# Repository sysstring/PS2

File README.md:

# PS2
LM317 based CC/CV power supply

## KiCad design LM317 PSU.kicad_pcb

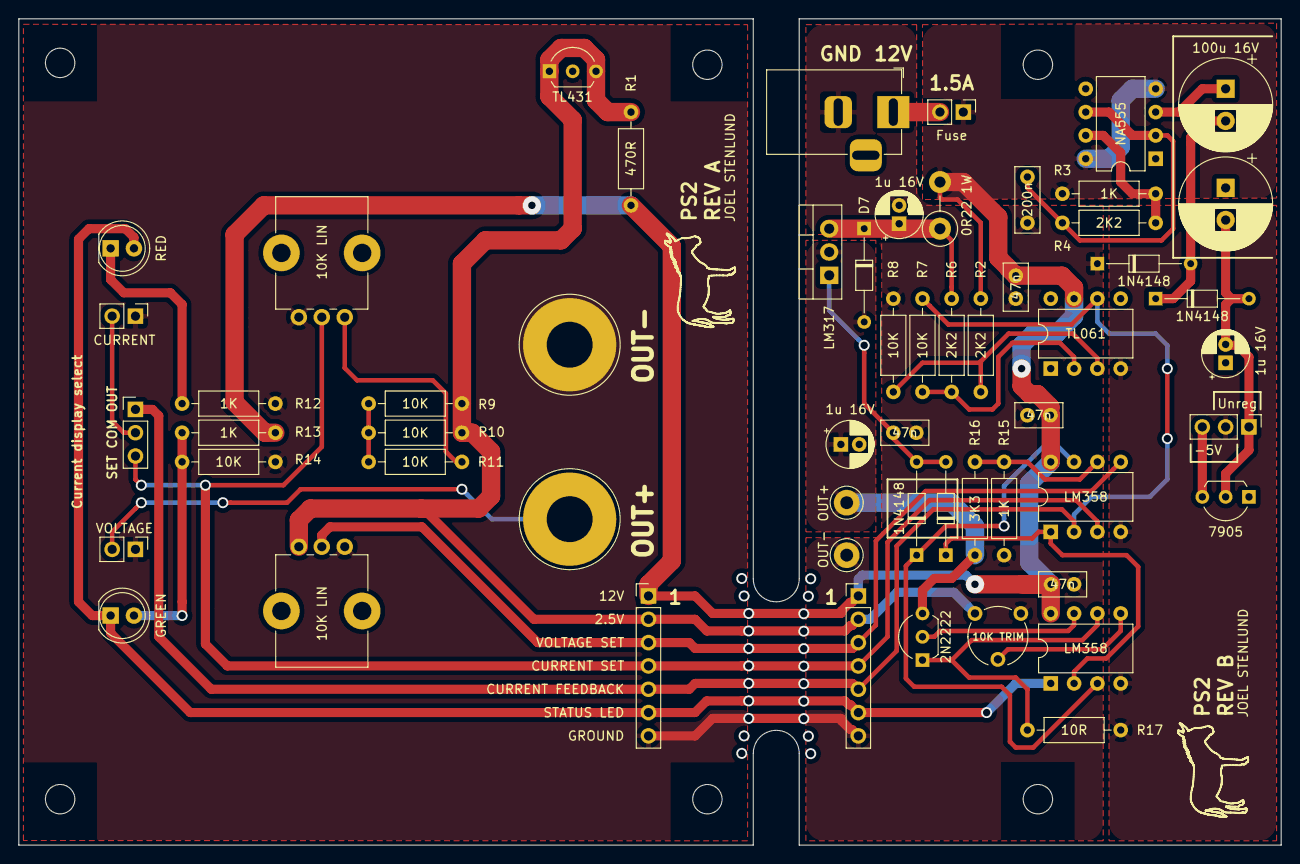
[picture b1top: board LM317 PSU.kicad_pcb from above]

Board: 2 copper layers, 137.5 x 90.0 mm, 63 parts (0 on the bottom side), 31 nets.

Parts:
C1: 200n; C_Rect_L7.0mm_W2.5mm_P5.00mm
C2: 100u 16V; CP_Radial_D10.0mm_P3.50mm
C3: 100u 16v; CP_Radial_D10.0mm_P3.50mm
C4, C6, C8, C9: 47n; C_Disc_D5.0mm_W2.5mm_P2.50mm
C5, C7, C10: 1u 16V; CP_Radial_D5.0mm_P2.00mm
D1: TL431; TO-92L_Inline_Wide
D2, D3, D6, D8: 1N4148; D_DO-34_SOD68_P10.16mm_Horizontal
D4: GREEN; LED_D5.0mm
D5: RED; LED_D5.0mm
D7: 1N4007; D_DO-34_SOD68_P10.16mm_Horizontal
F1: Fuse; PinHeader_1x02_P2.54mm_Vertical
J1: OUT+; Banana_Jack_1Pin
J2: OUT-; Banana_Jack_1Pin
J3: Barrel_Jack_MountingPin; BarrelJack_Horizontal
J4: Conn_01x07_Male; PinHeader_1x07_P2.54mm_Vertical
J5: Conn_01x07_Female; PinHeader_1x07_P2.54mm_Vertical
J7: Conn_01x01_Female; TestPoint_Loop_D3.50mm_Drill1.4mm_Beaded
J8: V- jumper; PinHeader_1x03_P2.54mm_Vertical
MES1: CURRENT; PinHeader_1x02_P2.54mm_Vertical
MES2: VOLTAGE; PinHeader_1x02_P2.54mm_Vertical
MH1, MH2, MH3, MH4, MH5, MH8: MountingHole; MountingHole_3.2mm_M3
OUT+: Conn_01x01_Female; TestPoint_Loop_D3.50mm_Drill1.4mm_Beaded
Q1: 2N2222; TO-92L_Inline_Wide
R1: 470R; R_Axial_DIN0207_L6.3mm_D2.5mm_P10.16mm_Horizontal
R2, R4, R6: 2K2; R_Axial_DIN0207_L6.3mm_D2.5mm_P10.16mm_Horizontal
R3, R12, R13, R16: 1K; R_Axial_DIN0207_L6.3mm_D2.5mm_P10.16mm_Horizontal
R5: 0R22 1W; R_Axial_DIN0411_L9.9mm_D3.6mm_P5.08mm_Vertical
R7, R8, R9, R10, R11, R14: 10K; R_Axial_DIN0207_L6.3mm_D2.5mm_P10.16mm_Horizontal
R15: 3K3; R_Axial_DIN0207_L6.3mm_D2.5mm_P10.16mm_Horizontal
R17: 10R; R_Axial_DIN0207_L6.3mm_D2.5mm_P10.16mm_Horizontal
RV1, RV2: 10K LIN; Potentiometer_Alps_RK09K_Single_Vertical
RV3: 10K TRIM; Potentiometer_Piher_PT-6-V_Vertical
SW1: Current display select; PinHeader_1x03_P2.54mm_Vertical
U1: NA555; DIP-8_W7.62mm
U2: TL061; DIP-8_W7.62mm
U3, U5: LM358; DIP-8_W7.62mm
U4: LM317; TO-220-3_Vertical
U6: 7905; TO-92L_Inline_Wide

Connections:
2V5: D1.1, D1.3, J4.2, J5.2, R1.1, R9.2, R10.2, RV2.1, RV3.1
12V_F: C4.2, C8.2, C9.2, F1.1, J4.1, J5.1, R1.2, R2.1, R3.1, R5.2, R13.1, U1.4, U1.8, U2.7, U3.8, U5.8
+12V: F1.2, J3.1
/Hi_side_sense: R2.2, R7.2, U2.3
/I_cmp: D6.1, U3.2, U5.1
/I_sink_sense: Q1.1, R17.2, U3.6
/Lo_side_sense: R6.2, R8.1, U2.2
/REG_INP: C5.1, D7.1, R5.1, R6.1, U4.3
/V_ADJ: C6.1, D6.2, D8.2, U4.1
/V_cmp: D8.1, U3.3, U5.7
GNDA: C1.1, C3.1, C4.1, C5.2, C6.2, C7.2, C8.1, C9.1, C10.1, D1.2, D3.1, J2.1, J3.2, J4.7, J5.7, J7.1, MES1.1, MES2.1, R7.1, R12.1, R14.1, R16.1, RV1.3, RV2.3, RV3.3, U1.1, U6.1
I_FB: J4.5, J5.5, R8.2, SW1.1, U2.6, U5.2
I_SET: J4.4, J5.4, RV1.2, SW1.3, U5.3
LED: D4.1, D5.2, J4.6, J5.6, U3.1
unnamed: C1.2, R4.2, U1.2, U1.6
unnamed: C2.1, U1.3
unnamed: C2.2, D2.1, D3.2
unnamed: C3.2, C10.2, D2.2, J8.1, U6.2
unnamed: D4.2, R13.2, R14.2
unnamed: D5.1, R12.2
unnamed: J8.3, U6.3
unnamed: MES1.2, SW1.2
unnamed: Q1.2, U3.7
unnamed: R3.2, R4.1, U1.7
unnamed: R9.1, R10.1, R11.1
unnamed: R11.2, RV1.1
unnamed: R15.1, R16.2, U5.6
unnamed: RV3.2, U3.5
OUTPUT: C7.1, D7.2, J1.1, MES2.2, OUT+.1, Q1.3, R15.2, U4.2
V-: J8.2, R17.1, U2.4, U3.4, U5.4
V_SET: J4.3, J5.3, RV2.2, U5.5

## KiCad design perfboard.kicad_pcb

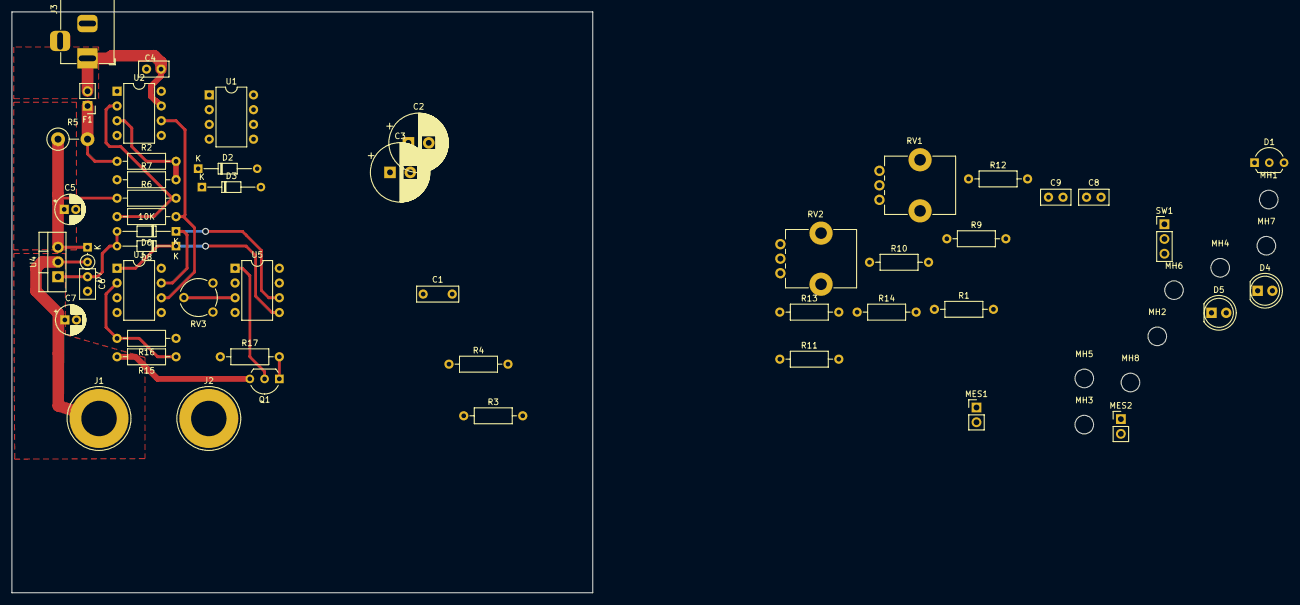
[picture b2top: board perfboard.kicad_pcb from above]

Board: 2 copper layers, 100.0 x 100.0 mm, 58 parts (0 on the bottom side), 29 nets.

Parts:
C1: 200n; C_Rect_L7.0mm_W2.5mm_P5.00mm
C2: 100u 16V; CP_Radial_D10.0mm_P3.50mm
C3: 100u 16v; CP_Radial_D10.0mm_P3.50mm
C4, C6, C8, C9: 47n; C_Disc_D5.0mm_W2.5mm_P2.50mm
C5, C7: 1u 16V; CP_Radial_D5.0mm_P2.00mm
D1: TL431LP 2V5 REF; TO-92L_Inline_Wide
D2, D3, D6, D8: 1N4148; D_DO-34_SOD68_P10.16mm_Horizontal
D4: GRN; LED_D5.0mm
D5: RED; LED_D5.0mm
D7: 1N4007; D_DO-34_SOD68_P2.54mm_Vertical_KathodeUp
F1: Fuse; PinHeader_1x02_P2.54mm_Vertical
J1: 4MM Red female; Banana_Jack_1Pin
J2: 4MM Black female; Banana_Jack_1Pin
J3: Barrel_Jack_MountingPin; BarrelJack_Horizontal
MES1: CURRENT; PinHeader_1x02_P2.54mm_Vertical
MES2: VOLTAGE; PinHeader_1x02_P2.54mm_Vertical
MH1, MH2, MH3, MH4, MH5, MH6, MH7, MH8: MountingHole; MountingHole_3.2mm_M3
Q1: 2N2222; TO-92L_Inline_Wide
R1: 470R; R_Axial_DIN0207_L6.3mm_D2.5mm_P10.16mm_Horizontal
R2, R4, R6: 2K2; R_Axial_DIN0207_L6.3mm_D2.5mm_P10.16mm_Horizontal
R3, R12, R13, R16: 1K; R_Axial_DIN0207_L6.3mm_D2.5mm_P10.16mm_Horizontal
R5: 0R22 1W; R_Axial_DIN0411_L9.9mm_D3.6mm_P5.08mm_Vertical
R7, R8, R9, R10, R11, R14: 10K; R_Axial_DIN0207_L6.3mm_D2.5mm_P10.16mm_Horizontal
R15: 3K3; R_Axial_DIN0207_L6.3mm_D2.5mm_P10.16mm_Horizontal
R17: 10R; R_Axial_DIN0207_L6.3mm_D2.5mm_P10.16mm_Horizontal
RV1, RV2: 10K LIN; Potentiometer_Alps_RK09K_Single_Vertical
RV3: 10K TRIM; Potentiometer_Piher_PT-6-V_Vertical
SW1: SW_Push_SPDT; PinHeader_1x03_P2.54mm_Vertical
U1: NA555; DIP-8_W7.62mm
U2: TL061; DIP-8_W7.62mm
U3, U5: LM358; DIP-8_W7.62mm
U4: LM317_3PinPackage; TO-220-3_Vertical

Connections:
2V5: D1.1, D1.3, R1.1, R9.2, R10.2, RV2.3, RV3.1
+12V: C4.2, C8.2, C9.2, F1.2, J3.1, R1.2, R3.1, R13.1, U1.4, U1.8, U2.7, U3.8, U5.8
/Hi_side_sense: R2.2, R7.2, U2.3
/I_cmp: D6.1, U3.7, U5.6
/I_sink_sense: Q1.1, R17.2, U5.2
/Lo_side_sense: R6.2, R8.1, U2.2
/REG_INP: C5.1, D7.1, R5.1, R6.1, U4.3
/V_ADJ: C6.1, D6.2, D8.2, U4.1
/V_cmp: D8.1, U3.1, U5.5
GNDA: C1.1, C3.1, C4.1, C5.2, C6.2, C7.2, C8.1, C9.1, D1.2, D3.1, J2.1, J3.2, MES1.1, MES2.1, R7.1, R12.1, R14.1, R16.1, RV1.1, RV2.1, RV3.3, U1.1
I_FB: R8.2, SW1.1, U2.6, U3.6
I_SET: RV1.2, SW1.3, U3.5
LED: D4.1, D5.2, U5.7
unnamed: C1.2, R4.2, U1.2, U1.6
unnamed: C2.1, D2.1, D3.2
unnamed: C2.2, U1.3
unnamed: D4.2, R13.2, R14.2
unnamed: D5.1, R12.2
unnamed: F1.1, R2.1, R5.2
unnamed: MES1.2, SW1.2
unnamed: Q1.2, U5.1
unnamed: R3.2, R4.1, U1.7
unnamed: R9.1, R10.1, R11.1
unnamed: R11.2, RV1.3
unnamed: R15.1, R16.2, U3.2
unnamed: RV3.2, U5.3
OUTPUT: C7.1, D7.2, J1.1, MES2.2, Q1.3, R15.2, U4.2
V-: C3.2, D2.2, R17.1, U2.4, U3.4, U5.4
V_SET: RV2.2, U3.3

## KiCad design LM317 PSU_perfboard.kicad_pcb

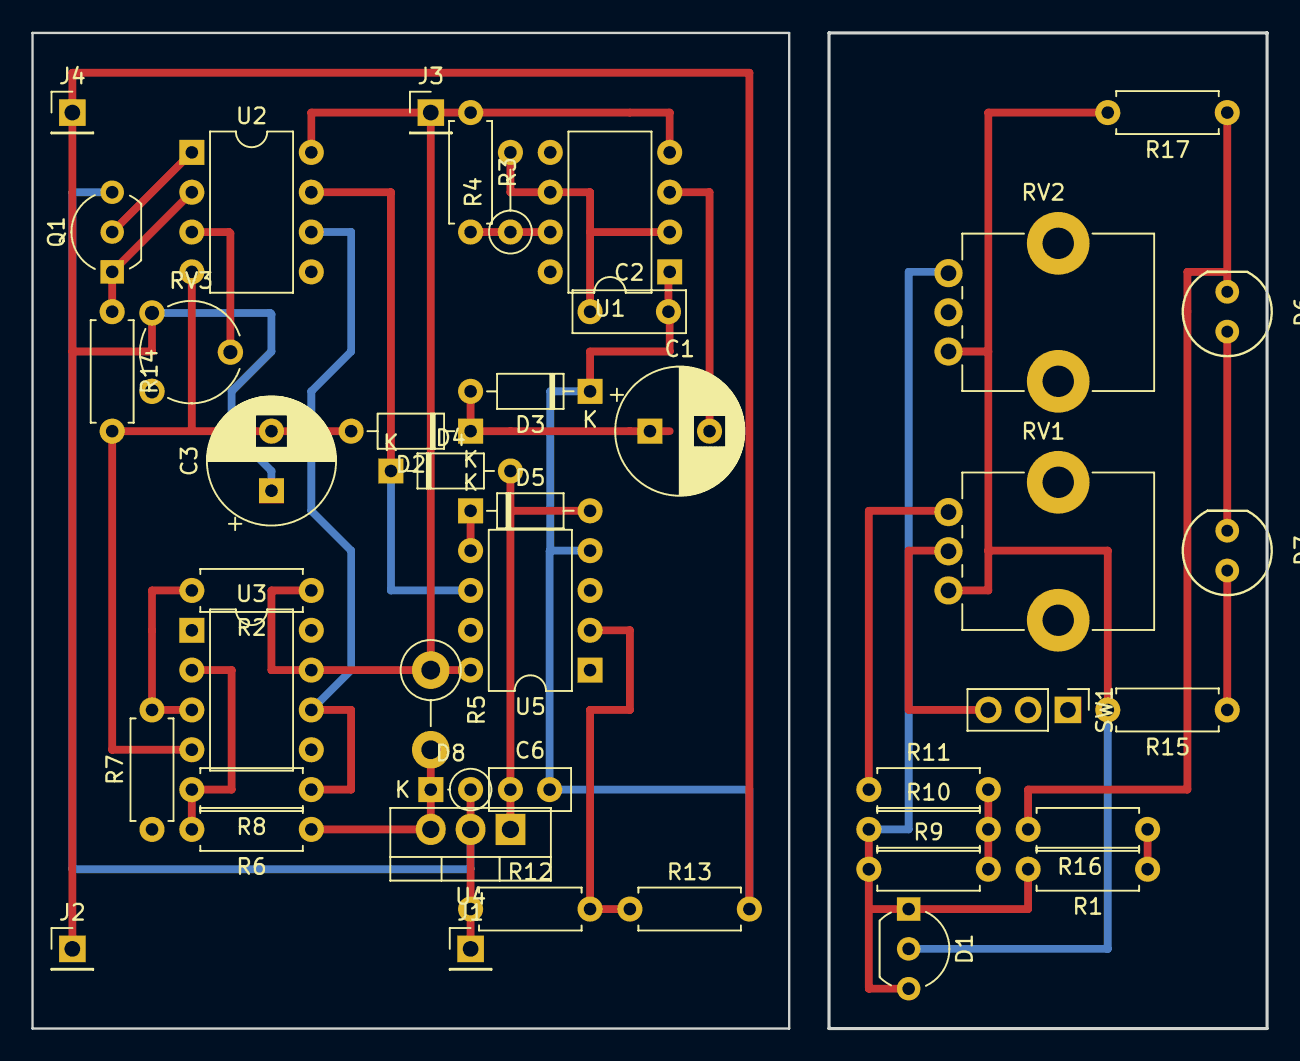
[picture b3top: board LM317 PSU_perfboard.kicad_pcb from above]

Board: 2 copper layers, 78.7 x 63.5 mm, 43 parts (0 on the bottom side), 27 nets.

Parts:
C1: 100u 16V; CP_Radial_D8.0mm_P3.80mm
C2: 200n; C_Rect_L7.0mm_W2.5mm_P5.00mm
C3: 100u 16v; CP_Radial_D8.0mm_P3.80mm
C6: 47n; C_Disc_D5.0mm_W2.5mm_P2.50mm
D1: TL431LP 2V5 REF; TO-92_Inline_Wide
D2, D3, D4, D5: 1N4148; D_DO-35_SOD27_P7.62mm_Horizontal
D6: 5MM Green; 5MM_LED
D7: 5MM Red; 5MM_LED
D8: 1N4007; D_DO-35_SOD27_P2.54mm_Vertical_KathodeUp
J1: 4MM Red female; PinHeader_1x01_P2.54mm_Vertical
J2: 4MM Black female; PinHeader_1x01_P2.54mm_Vertical
J3: V_IN; PinHeader_1x01_P2.54mm_Vertical
J4: GND; PinHeader_1x01_P2.54mm_Vertical
Q1: 2N2222; TO-92_Inline_Wide
R1: 470R; R_Axial_DIN0207_L6.3mm_D2.5mm_P7.62mm_Horizontal
R2, R6: 2.2K; R_Axial_DIN0207_L6.3mm_D2.5mm_P7.62mm_Horizontal
R3, R13, R15, R16: 1K; R_Axial_DIN0207_L6.3mm_D2.5mm_P7.62mm_Horizontal
R4: 2.2K; R_Axial_DIN0207_L6.3mm_D2.5mm_P5.08mm_Vertical
R5: 0R22 1W MIN; R_Axial_DIN0411_L9.9mm_D3.6mm_P5.08mm_Vertical
R7, R8, R9, R10, R11, R17: 10K; R_Axial_DIN0207_L6.3mm_D2.5mm_P7.62mm_Horizontal
R12: 3.3K; R_Axial_DIN0207_L6.3mm_D2.5mm_P7.62mm_Horizontal
R14: 10R; R_Axial_DIN0207_L6.3mm_D2.5mm_P7.62mm_Horizontal
RV1, RV2: 10K LIN; Potentiometer_Alps_RK09K_Single_Vertical
RV3: 10K TRIM; Potentiometer_Piher_PT-6-V_Vertical
SW1: SW_Push_SPDT; PinHeader_1x03_P2.54mm_Vertical
U1: NA555; DIP-8_W7.62mm
U2, U5: LM358; DIP-8_W7.62mm
U3: TL061; DIP-8_W7.62mm
U4: LM317_3PinPackage; TO-220-3_Vertical

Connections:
2V5: D1.1, D1.3, R1.2, R9.1, R10.1, RV2.3, RV3.1
+12V: J3.1, R1.1, R2.1, R3.1, R5.1, R16.1, U1.4, U1.8, U2.8, U3.7, U5.8
/Hi_side_sense: R2.2, R7.2, U3.3
/I_SENSE: R8.1, SW1.1, U2.6, U3.6
/I_set: D4.1, U2.7, U5.6
/I_sink_sense: Q1.1, R14.1, U2.2
/Lo_side_sense: R6.2, R8.2, U3.2
/OUTPUT: D8.2, J1.1, Q1.3, R12.1, U4.2
/REG_INP: D8.1, R5.2, R6.1, U4.3
/V_ADJ: C6.1, D4.2, D5.2, U4.1
/V_set: D5.1, U5.1, U5.5
GNDA: C2.2, C3.1, C6.2, D1.2, D3.1, J2.1, J4.1, R7.1, R13.2, R15.2, R17.2, RV1.1, RV2.1, RV3.3, U1.1, U5.4
I_SET: RV1.2, SW1.3, U2.5
unnamed: C1.1, D2.1, D3.2
unnamed: C1.2, U1.3
unnamed: C2.1, R4.2, U1.2, U1.6
unnamed: D6.1, D7.2, U5.7
unnamed: D6.2, R16.2, R17.1
unnamed: D7.1, R15.1
unnamed: Q1.2, U2.1
unnamed: R3.2, R4.1, U1.7
unnamed: R9.2, R10.2, R11.2
unnamed: R11.1, RV1.3
unnamed: R12.2, R13.1, U5.2
unnamed: RV3.2, U2.3
V-: C3.2, D2.2, R14.2, U2.4, U3.4
V_SET: RV2.2, U5.3

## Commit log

2019-09-19 Added all files from project
2019-09-19 Replaced custom symbols with generic ones
2019-09-21 Started laying out PCB
2019-09-22 main board almost complete
2019-09-23 put all 12V inputs after the fuse
2019-09-24 Rev 1 mostly complete
2019-09-24 added cut outs for meters, started arranging silkscreen
2019-09-26 REV B SENT FOR PROTOTYPING, ADDED NEG RAIL REGULATOR
2019-09-28 fixed broken silkscreen
2019-10-17 REV C schematic
